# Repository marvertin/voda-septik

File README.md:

# voda-septik

Repozitář obsahuje ESP-IDF firmware a KiCad návrh hardware. Provozní dokumentace je v [firmware/README.md](firmware/README.md).

## Struktura

- `firmware/main/` – aplikace; `main/archive/` obsahuje historický referenční kód.
- `firmware/components/` – vlastní komponenty.
- `firmware/managed_components/` – externí knihovny, jejichž obsah je uložený v Gitu.
- `firmware/dependencies.lock` – přesné verze externích závislostí.
- `firmware/sdkconfig` – úplná konfigurace sestavení pro ESP32.
- `firmware/sdkconfig.defaults` – doplňující výchozí nastavení.
- `firmware/partitions.csv` – rozdělení 4MB flash paměti.
- `firmware/tools/zalevaci` – nástroj pro MQTT příkazy, diagnostiku a OTA.
- `firmware/ha/` – [podklady pro vytvoření a obnovu provozu HA a MQTT](firmware/ha/README.md), dvě samostatné Compose služby a verzovaná konfigurace bez provozních hesel.
- `hardware/` – KiCad projekt, schéma, PCB a vlastní knihovny; mapa v [hardware/README.md](hardware/README.md).
- `AGENTS.md` a `.agents/` – pracovní instrukce a mapy projektu.

## Verze a větve

- Firmware: **ESP-IDF v5.5.2**, target **esp32**. Stejnou verzi používá automatické sestavení v `.github/workflows/build.yml`.
- Hardware byl upravován v **KiCadu 9**.
- Nová funkcionalita vzniká na dočasné větvi `develop` vytvořené z `main`, nasazuje se přes USB/OTA a testuje. Po potvrzení OTA se `main` posune na skutečně provozovaný commit. Provozní opravy vznikají na `main` a ihned se nasazují; následně se přenesou do develop, pokud existuje. Po začlenění a ověření se develop smaže. Čistá dokumentace patří na main a případně existující develop bez zvýšení release verze. Úplný postup a mechanismus Git verzí jsou v [pravidlech vývoje a nasazení](firmware/docs/vyvoj-a-nasazeni.md).

Obnovu začni z `main`, pokud nepotřebuješ konkrétní vývojovou verzi. IDF ani verze knihoven se při obnově automaticky neaktualizují na novější řadu.

## Obnova na čistém počítači

### 1. Získání projektu

Nainstaluj Git a zajisti přístup ke GitHub repozitáři. Na macOS/Linuxu:

```sh
mkdir -p ~/Projects
cd ~/Projects
git clone git@github.com:marvertin/voda-septik.git
cd voda-septik
git switch main
```

Pokud nemáš nastavený SSH klíč, použij HTTPS adresu `https://github.com/marvertin/voda-septik.git` a přihlas se ke GitHubu. SSH klíče nejsou součástí tohoto repozitáře.

### 2. Instalace ESP-IDF

Použij [oficiální instalační postup pro ESP-IDF v5.5.2](https://docs.espressif.com/projects/esp-idf/en/v5.5.2/esp32/get-started/index.html) včetně systémových předpokladů pro svůj operační systém.

Pro ruční instalaci na macOS/Linuxu do umístění očekávaného projektovým `.envrc`:

```sh
mkdir -p ~/.espressif/v5.5.2
git clone --branch v5.5.2 --recursive https://github.com/espressif/esp-idf.git ~/.espressif/v5.5.2/esp-idf
cd ~/.espressif/v5.5.2/esp-idf
./install.sh esp32
```

Na Windows vyber ve vhodném instalátoru nebo rozšíření ESP-IDF verzi **v5.5.2** a otevři jeho připravený terminál. Projektové `.envrc` je určené pro macOS/Linux, není podmínkou sestavení.

Instalace IDF, překladače a Python prostředí jsou obnovitelné nástroje a do projektového Gitu nepatří.

### 3. Sestavení

Na macOS/Linuxu aktivuj IDF pro aktuální terminál:

```sh
source ~/.espressif/v5.5.2/esp-idf/export.sh
cd ~/Projects/voda-septik/firmware
idf.py --version
idf.py build
```

Ověř, že první příkaz vypíše verzi **5.5.2**. Target `esp32` je již uložený v `sdkconfig`; při obnově není potřeba spouštět `idf.py set-target`, který resetuje konfiguraci.

Výstup je `firmware/build/voda-septik.bin`. Složka `build/` se vytváří znovu a nezálohuje se v Gitu. Po přesunu projektu odstraň staré `build/`, aby nezůstaly absolutní cesty z původního umístění.

Volitelně lze použít `direnv`: nainstaluj ho, zapoj do svého shellu a v `firmware/` spusť `direnv allow`. Projektový `.envrc` přidá i `firmware/tools` do `PATH`. Při jiném umístění IDF uprav jeho cestu nebo aktivuj IDF ručně.

### 4. Nahrání přes USB

Připoj ESP32 a zjisti jeho sériový port. Z `firmware/` spusť:

```sh
idf.py -p PORT flash monitor
```

Nahraď `PORT` skutečným portem, například `/dev/cu.usbserial-…` na macOS nebo `COM3` na Windows. Monitor se ukončuje pomocí `Ctrl+]`.

Pro nahrání používej projektovou tabulku oddílů a sestavený bootloader. Příkaz `erase-flash` smaže také nastavení a provozní hodnoty uložené v zařízení; pro běžnou obnovu počítače není potřeba.

## MQTT a OTA

Nástroj `tools/zalevaci` vyžaduje Python 3; pro MQTT operace také příkazy `mosquitto_pub` a pro OTA `mosquitto_sub`. Spouštěj jej ze složky `firmware/`:

```sh
./tools/zalevaci --help
./tools/zalevaci ota --help
```

Broker a přihlašování lze nastavit parametry nástroje nebo proměnnými prostředí, například `MQTT_HOST`, `MQTT_PORT`, `MQTT_USER` a `MQTT_PASS_FILE`. Výchozí adresy brokerů jsou lokální pro původní síť a na jiném místě je potřeba je změnit.

MQTT heslo si nástroj ukládá do `~/.voda-septik/mqtt_password`. Tento soubor **není v repozitáři**: heslo uchovej ve správci hesel nebo bezpečné záloze. Nástroj si při prvním použití vyžádá chybějící heslo. Heslo nezapisuj do README ani jej nepřidávej do Gitu.

OTA používá MQTT příkazy a HTTP(S) stažení obrazu. Nový firmware po ověření funkčnosti vyžaduje potvrzení kvůli rollbacku. Aktuální rozhraní helperu popisuje `./tools/zalevaci ota --help`; interaktivní i neinteraktivní postup a rollback popisuje [firmware/docs/ota.md](firmware/docs/ota.md).

## Obnova hardware v KiCadu

1. Nainstaluj KiCad 9 a jeho standardní knihovny.
2. Otevři `hardware/Voda septik.kicad_pro`.
3. Projektové tabulky `sym-lib-table` a `fp-lib-table` připojují knihovnu `martin` přes `${KIPRJMOD}`. Díky tomu nezávisí na absolutní cestě k projektu.
4. Přes správce zásuvných modulů a obsahu nainstaluj **Espressif KiCad Libraries**. Návrh používá knihovnu s názvem `PCM_Espressif`; ověř její registraci v tabulce symbolů i footprintů. Pokud chybí, připoj odpovídající nainstalovanou knihovnu pod tímto názvem.

Použité symboly a footprinty jsou vložené také ve schématu a PCB, takže existující návrh lze otevřít. Pro aktualizace z knihoven a vkládání dalších součástek je potřeba správně připojit externí knihovny. Verze balíčku Espressif zatím není v projektu připnutá.

Automatické zálohy KiCadu, zámky a osobní nastavení editoru se v Gitu neuchovávají.

## Co zálohovat mimo Git

Git uchovává zdroje a konfiguraci pro sestavení, nikoli celý provozní stav:

- MQTT heslo a případné další přístupové údaje uložené mimo repozitář.
- Nastavení, kalibrace a čítače v ESP32: NVS a datové oddíly zařízení nejsou součástí zdrojového kódu. Pro úplnou obnovu zařízení udržuj samostatný záznam nastavení nebo zálohu jeho datových oddílů.
- Při provozování Home Assistantu také jeho úplnou zálohu. Git obsahuje YAML konfiguraci, ale ne `.storage`, databázi, uživatele a nastavení vytvořená přes UI. Obdobně případná provozní data Mosquitto vyžadují vlastní zálohu.

Konfigurace Docker Compose používá pohyblivé značky obrazů `stable` a `2`; sama nezaručuje obnovu totožné verze služeb.

Lokální commity, necommitované soubory a stashe nejsou automaticky na GitHubu. Po dokončení změn je commitni a odešli do příslušné větve. Stav ověř pomocí `git status`, `git fetch origin` a `git branch -vv`.

## Ověření obnovitelnosti

Dne **12. 10. 2026** byl nový klon větve `main` z GitHubu sestaven bez původní složky `build/` a bez necommitovaných souborů projektu. Sestavení s ESP-IDF **5.5.2** pro **ESP32** prošlo. Test použil již nainstalované nástroje; nová instalace vývojového prostředí ani flashování fyzického zařízení nebyly součástí testu.

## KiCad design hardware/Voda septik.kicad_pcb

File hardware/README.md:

# Hardware voda-septik

Stav dokumentace ověřen 12. 10. 2026. Návrh je v KiCadu 9 a související runtime firmware je v `../firmware/`.

## Soubory a knihovny

- `Voda septik.kicad_pro` – projekt; `Voda septik.kicad_sch` – schéma; `Voda septik.kicad_pcb` – deska.
- `martin.kicad_sym` a `martin.pretty/` jsou připojené jako projektová knihovna `martin` pomocí `${KIPRJMOD}`.
- `0martin.kicad_sym` a `zaciname.pretty/` jsou také v Gitu, ale současné projektové tabulky je nepřipojují jako samostatné knihovny.
- Standardní KiCad knihovny používané návrhem zahrnují `Device`, `Connector`, `Analog_ADC`, `Display_Character`, `power`, `Capacitor_THT`, `Connector_PinHeader_2.54mm`, `Diode_THT`, `LED_THT`, `Resistor_THT`.
- Externí **Espressif KiCad Libraries** nainstaluj přes správce zásuvných modulů a obsahu a ověř registraci názvu `PCM_Espressif` v tabulce symbolů i footprintů. Balíček není v repozitáři ani připnutý na konkrétní verzi.
- Schéma/PCB obsahují vložené kopie použitých symbolů/footprintů. To umožňuje otevřít stávající návrh, ale pro aktualizace a nové součástky je potřeba dostupná zdrojová knihovna.
- `.kicad_prl`, zámky a automatické zálohy jsou ignorované; `.bak`, stará schématická záloha, CSV a `fp-info-cache` jsou historicky verzované pomocné soubory.

## GPIO podle aktivního firmware

Zdrojem této tabulky je [pins.h](../firmware/main/pins.h); jde o konfiguraci programu, nikoli nezávislé elektrické ověření zapojení desky.

| Konstanta | GPIO | Poznámka v kódu |
| --- | --- | --- |
| `STATUS_LED_GPIO` | 16 | D9 LED |
| `TM1637_CLK_GPIO` | 17 | J4 CLK |
| `TM1637_DIO_GPIO` | 18 | J4 DIO |
| `DISPLAY_I2C_SDA_GPIO` | 22 | J3 SDA |
| `DISPLAY_I2C_SCL_GPIO` | 23 | J3 SCL |
| `ADS1115_I2C_SDA_GPIO` | 14 | U3 SDA |
| `ADS1115_I2C_SCL_GPIO` | 13 | U3 SCL |
| `ADS1115_ALERT_RDY_GPIO` | 4 | U3 ALERT/RDY |
| `FLOW_SENSOR_GPIO` | 33 | /prutok |
| `TEMPERATURE_SENSOR_GPIO` | 32 | /teplomery |
| `RS485_RX_GPIO` | 27 | MAX3485 TXD |
| `RS485_TX_GPIO` | 26 | MAX3485 RXD |
| `RS485_EN_GPIO` | 25 | MAX3485 EN |
| `BOOT_BUTTON_GPIO` | 0 | GPIO0 |

## Sběrnice a ADC

- ADS1115: I2C0, adresa **0x48**, 100 kHz, SDA14/SCL13, ALERT/RDY4. Jediný ADC task přepíná single-ended kanály: AIN1 tlak za filtrem, AIN2 tlak před filtrem, AIN3 hladina; AIN0 je rezerva.
- LCD HD44780 / PCF8574: samostatné I2C1, adresa **0x27**, SDA22/SCL23. Nezaměňuj ji s ADC sběrnicí.
- Proudové smyčky: firmware předpokládá **100Ω shunt**, PGA ADS1115 **±2,048 V**, LSB 62,5 µV; 4 mA → 0,4 V → RAW6400, 20 mA → 2,0 V → RAW32000. Kalibrace se ukládá v zařízení.
- RS485 / KWS-303L: UART2, **9600 8N1**, RX27/TX26, řízení směru 25, výchozí slave adresa 1.
- DS18B20: sdílená 1-Wire na GPIO32; voda a vzduch se rozlišují podle ROM adres.
- Průtok: náběžná hrana na GPIO33, výchozí 38 impulsů/l; nejde o analogový vstup.
- TM1637: CLK17/DIO18; BOOT je GPIO0, status LED GPIO16.

## Flash paměť

ESP32 má v projektu konfiguraci 4 MB. Zdrojem je [partitions.csv](../firmware/partitions.csv):

| Oddíl | Offset | Velikost | Účel |
| --- | --- | --- | --- |
| `nvs` | 0x9000 | 0x6000 | konfigurace `app_cfg`, restart metadata `sys_meta`, základ čítače `flash_ctr` |
| `otadata` | 0xF000 | 0x2000 | volba OTA obrazu |
| `phy_init` | 0x11000 | 0x1000 | PHY data |
| `flow_data0` | 0x12000 | 0x2000 | bitový flash čítač celých litrů |
| `user_data1` | 0x14000 | 0x2000 | rezervovaný datový oddíl |
| `user_data2` | 0x16000 | 0x2000 | rezervovaný datový oddíl |
| `user_data3` | 0x18000 | 0x2000 | rezervovaný datový oddíl |
| `ota_0` | 0x20000 | 0x180000 | první obraz aplikace |
| `ota_1` | 0x1A0000 | 0x180000 | druhý obraz aplikace |

Při obnově čítače nestačí samotný `flow_data0`: potřebuje i základ/rollover marker z NVS `flash_ctr`. Při přemapování oddílů, změně ADC rozsahu, adres nebo GPIO aktualizuj firmware i tuto mapu. Dokumentační průchod neprováděl měření skutečné desky.

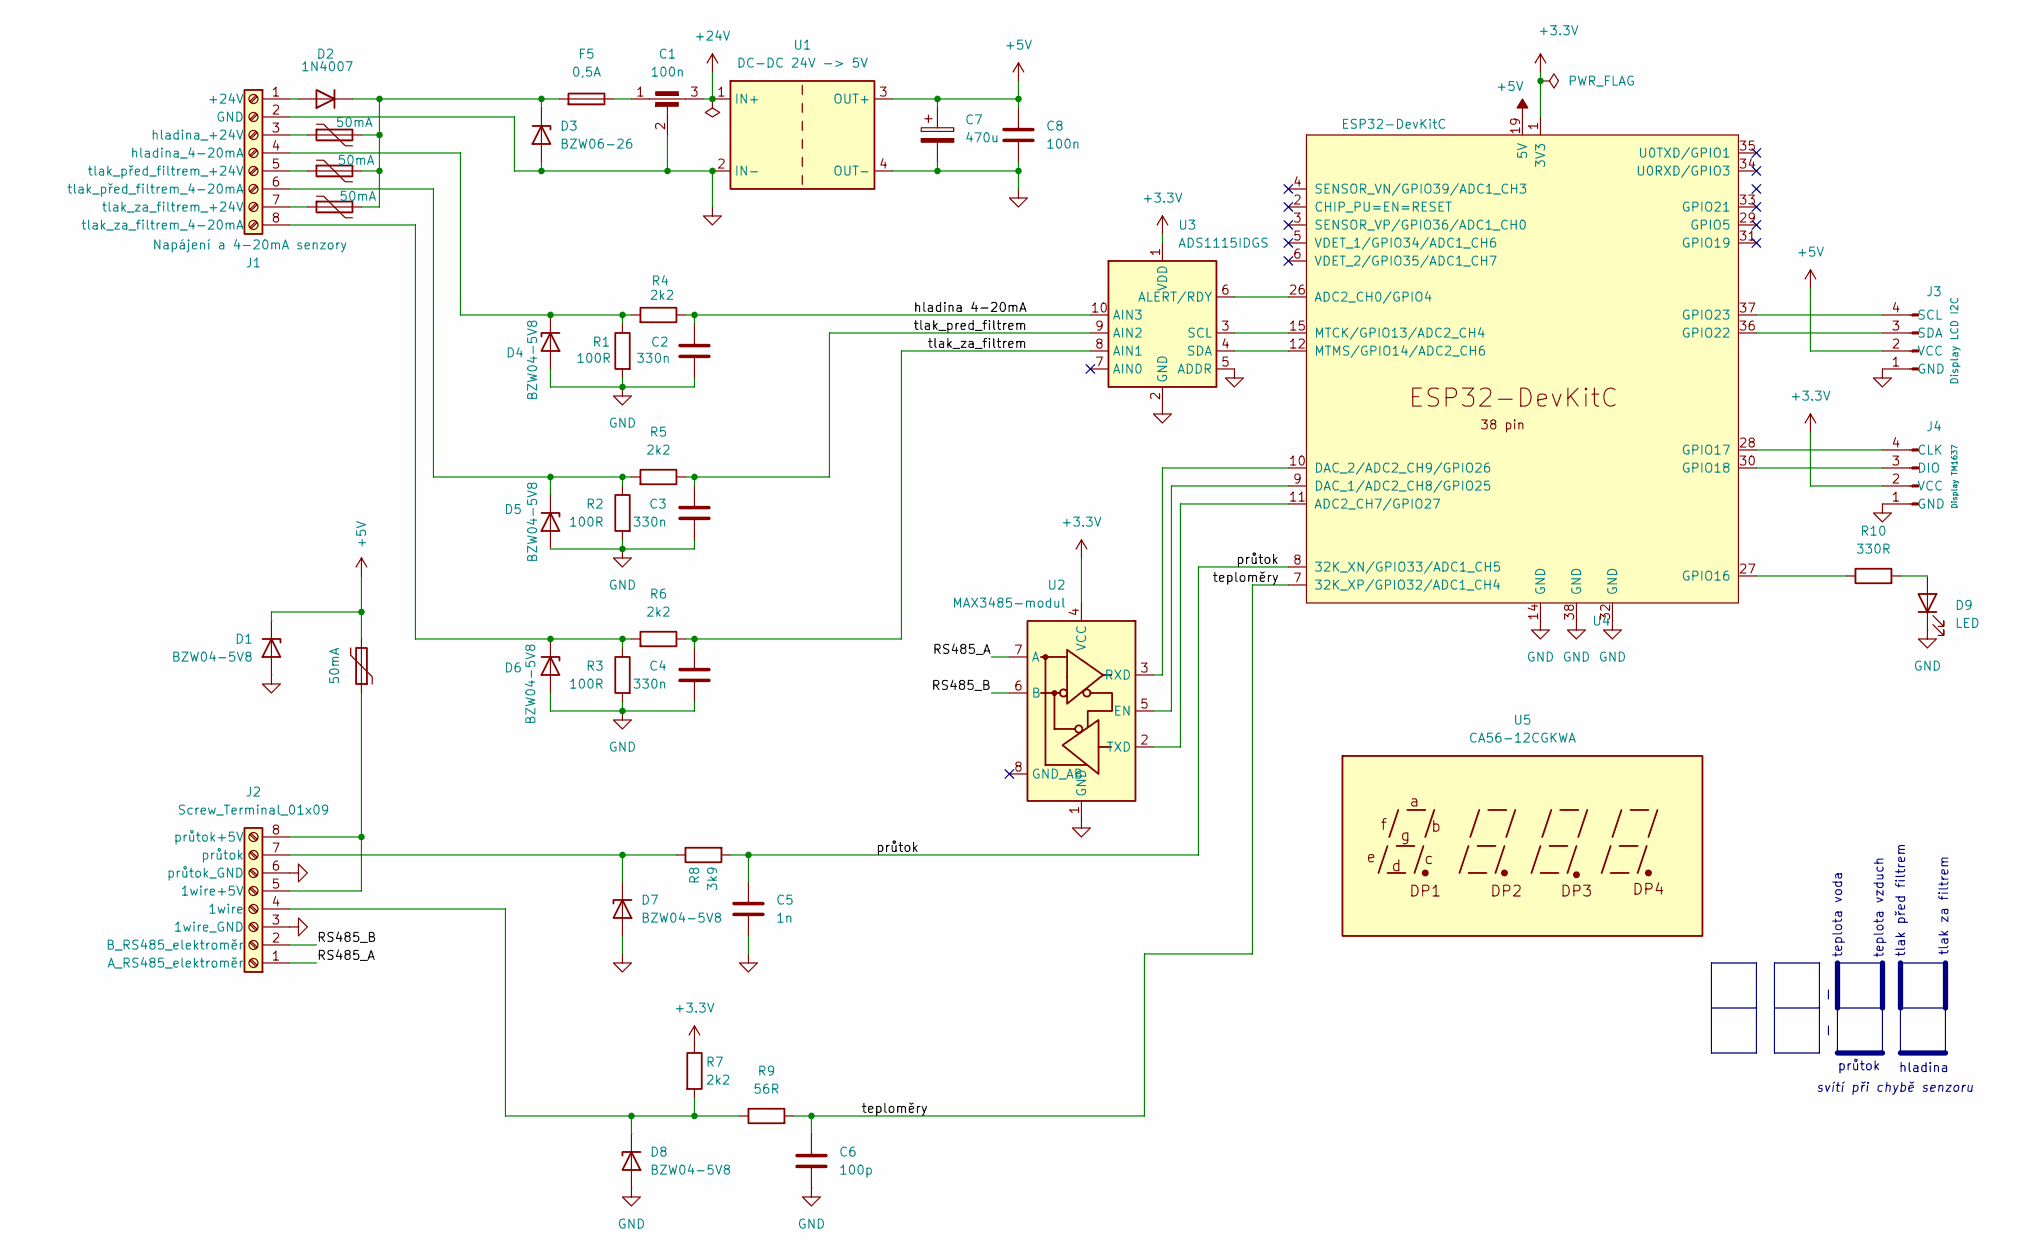
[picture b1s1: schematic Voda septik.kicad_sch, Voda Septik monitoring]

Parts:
C1: 100n; Odruseni_3x_2.54mm
C2, C3, C4: 330n; C_Disc_D5.0mm_W2.5mm_P5.00mm
C5: 1n; C_Disc_D5.0mm_W2.5mm_P5.00mm
C6: 100p; C_Disc_D5.0mm_W2.5mm_P5.00mm
C7: 470u; CP_Radial_D10.0mm_P5.00mm
C8: 100n; C_Disc_D5.0mm_W2.5mm_P5.00mm
D1, D4, D5, D6, D7, D8: BZW04-5V8; D_DO-15_P2.54mm_Vertical_AnodeUp
D2: 1N4007; D_DO-15_P2.54mm_Vertical_AnodeUp
D3: BZW06-26; D_DO-15_P2.54mm_Vertical_AnodeUp
D9: LED; LED_D3.0mm
F1, F2, F3, F4: 50mA; Fuse_Disc_D8.3_W3.8_P5.1
F5: 0,5A; Fuse_Axial_L11mm_D3.9mm_P15.24mm_Horizontal
J1: Napájení a 4-20mA senzory; Svorky_EB147A_8_5.08
J2: Screw_Terminal_01x09; Svorky_EB147A_8_5.08
J3: Display LCD I2C; PinHeader_1x04_P2.54mm_Vertical
J4: Display TM1637; PinHeader_1x04_P2.54mm_Vertical
R1, R2, R3: 100R; R_Axial_DIN0207_L6.3mm_D2.5mm_P2.54mm_Vertical
R4, R5, R6, R7: 2k2; R_Axial_DIN0207_L6.3mm_D2.5mm_P2.54mm_Vertical
R8: 3k9; R_Axial_DIN0207_L6.3mm_D2.5mm_P2.54mm_Vertical
R9: 56R; R_Axial_DIN0207_L6.3mm_D2.5mm_P2.54mm_Vertical
R10: 330R; R_Axial_DIN0207_L6.3mm_D2.5mm_P2.54mm_Vertical
U1: DC-DC 24V -> 5V; LM2596 DC-DC HW-411
U2: MAX3485-modul
U3: ADS1115IDGS; ADS1115_modul_vertical
U4: ESP32-DevKitC
U5: CA56-12CGKWA; DISPLAY_clok_MOUNT_4xM3

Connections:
+3.3V: J4.2 (VCC), R7.1, U2.4 (VCC), U3.1 (VDD), U4.1 (3V3)
+5V: C7.1, C8.1, D1.1 (K), F4.2, J3.2 (VCC), U1.3 (OUT+), U4.19 (5V)
+24V: C1.3, U1.1 (IN+)
/RS485_A: J2.1 (A_RS485_elektroměr), U2.7 (A)
/RS485_B: J2.2 (B_RS485_elektroměr), U2.6 (B)
/hladina 4-20mA: C2.1, R4.1, U3.10 (AIN3)
/průtok: C5.1, R8.2, U4.8 (32K_XN/GPIO33/ADC1_CH5)
/teploměry: C6.1, R9.2, U4.7 (32K_XP/GPIO32/ADC1_CH4)
/tlak_pred_filtrem: C3.1, R5.1, U3.9 (AIN2)
/tlak_za_filtrem: C4.1, R6.1, U3.8 (AIN1)
GND: C1.2, C2.2, C3.2, C4.2, C5.2, C6.2, C7.2, C8.2, D1.2 (A), D3.2 (A), D4.2 (A), D5.2 (A), D6.2 (A), D7.2 (A), D8.2 (A), D9.1 (K), J1.2 (GND), J2.3 (1wire_GND), J2.6 (průtok_GND), J3.1 (GND), J4.1 (GND), R1.2, R2.2, R3.2, U1.2 (IN-), U1.4 (OUT-), U2.1 (GND), U3.2 (GND), U3.5 (ADDR), U4.14 (GND), U4.32 (GND), U4.38 (GND)
unnamed: C1.1, F5.2
unnamed: D2.2 (A), J1.1 (+24V)
unnamed: D2.1 (K), D3.1 (K), F1.2, F2.2, F3.2, F5.1
unnamed: D4.1 (K), J1.4 (hladina_4-20mA), R1.1, R4.2
unnamed: D5.1 (K), J1.6 (tlak_před_filtrem_4-20mA), R2.1, R5.2
unnamed: D6.1 (K), J1.8 (tlak_za_filtrem_4-20mA), R3.1, R6.2
unnamed: D7.1 (K), J2.7 (průtok), R8.1
unnamed: D8.1 (K), J2.4 (1wire), R7.2, R9.1
unnamed: D9.2 (A), R10.2
unnamed: F1.1, J1.3 (hladina_+24V)
unnamed: F2.1, J1.5 (tlak_před_filtrem_+24V)
unnamed: F3.1, J1.7 (tlak_za_filtrem_+24V)
unnamed: F4.1, J2.5 (1wire+5V), J2.8 (průtok+5V)
unnamed: J3.4 (SCL), U4.37 (GPIO23)
unnamed: J3.3 (SDA), U4.36 (GPIO22)
unnamed: J4.4 (CLK), U4.28 (GPIO17)
unnamed: J4.3 (DIO), U4.30 (GPIO18)
unnamed: U2.5 (EN), U4.9 (DAC_1/ADC2_CH8/GPIO25)
unnamed: U2.3 (RXD), U4.10 (DAC_2/ADC2_CH9/GPIO26)
unnamed: U2.2 (TXD), U4.11 (ADC2_CH7/GPIO27)
unnamed: U3.6 (ALERT/RDY), U4.26 (ADC2_CH0/GPIO4)
unnamed: U3.3 (SCL), U4.15 (MTCK/GPIO13/ADC2_CH4)
unnamed: U3.4 (SDA), U4.12 (MTMS/GPIO14/ADC2_CH6)
unnamed: R10.1, U4.27 (GPIO16)

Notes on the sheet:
teplota vzduch
průtok
tlak před filtrem
svítí při chybě senzoru
tlak za filtrem
teplota voda
hladina

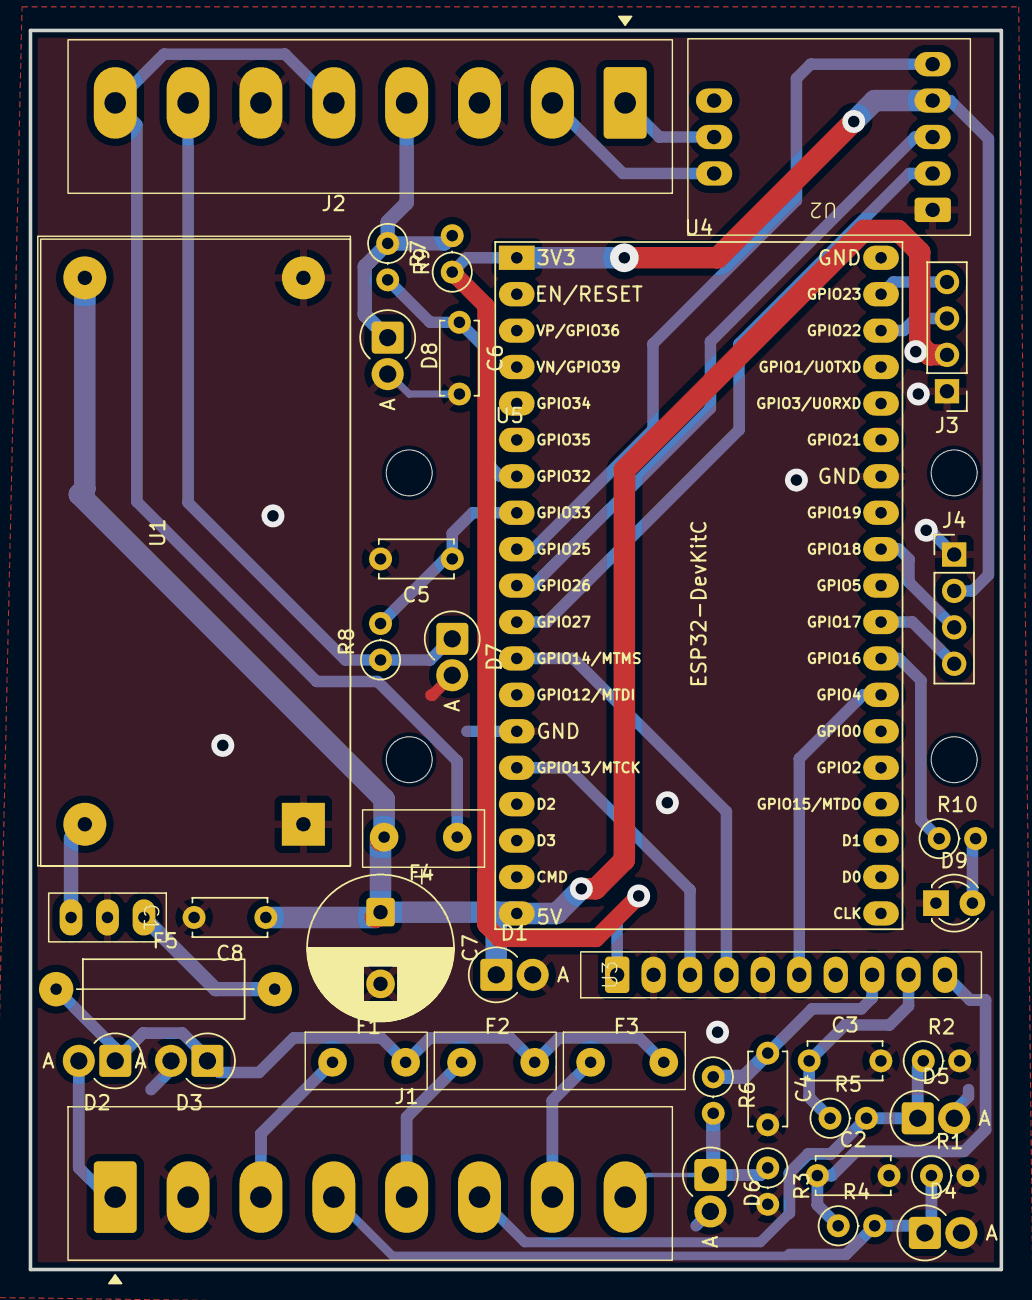
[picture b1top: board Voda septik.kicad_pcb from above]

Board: 2 copper layers, 67.7 x 86.4 mm, 41 parts (0 on the bottom side), 35 nets.

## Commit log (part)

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2026-02-11 Měření výšky hladiny.
2026-02-11 Instalace ESP_IDF přes eim install
2026-02-12 Zapisujeme na displej všechny veličiny.
2026-02-12 Funguje nějak oříznutý plovoucí průměr.
2026-02-12 Převedení do C++
2026-02-12 Převedení ořezaného průmeru na třídu.
2026-02-12 Vyřešení špatné inicializace.
2026-02-12 Inicializace wifi
2026-02-12 Heslo bere z flash.
2026-02-13 Rozchození publikace přes mqtt do HA.
2026-02-14 Konfigurační aplikace.
2026-02-14 Změna načítání configu.
2026-02-14 Počítání restartů a úvodní stránka.
2026-02-15 Příznak servisního režimu.
2026-02-15 Výpis ota partišnů.
2026-02-15 Předělán průtokoměr.
2026-02-15 Průtokoměr nějak funguje.
2026-02-15 ODstranění _demo z průtokoměru.
2026-02-22 Přidat eventy na stavy sítě.
2026-02-22 MQTT se opět nějak publikuje.
2026-02-22 Méžná o něco lepší synchronizace.
2026-02-22 Inicializace sítě architektonicky upravena, včetně MQTT.
2026-02-22 Refaktorována síť do komponenty.
2026-02-22 Už to lépe posílá offline a online statusy.
2026-02-22 Odstranit nekonečný reconnect.
2026-02-22 Vyčištení přijímání network eventů.
2026-02-22 Publikovat online mimo network_core.
2026-02-22 Úprava topiků.
2026-02-22 Při stisku boot tlačítka se otevře access point.
2026-02-22 Captive DNS funguje.
2026-02-22 Jména logovacích tagů malými písmeny.
2026-02-22 Zjednodušit začátek, žádný AP mód.
2026-02-22 Boot tlačítko v samostatném souboru.
2026-02-22 Posílání události do state managera.
2026-02-22 Blokovat rekonet v access pointu.
2026-02-22 Počítání pokusů o reconnect a úspěšných reconnectů.
2026-02-22 Vyčlenění access pointovin do jiného souboru.
2026-02-22 Ošetření chyb konzistentně.
2026-02-22 Velký refactoring, ale máme problém se čtením z nvs.
2026-02-22 Operaveno startování webové apliakce.
2026-02-22 Už se správně inicializuje mqtt
2026-02-22 Posílání RSSI
2026-02-23 10 sekund zuřivého blikání po chybě.
2026-02-23 Zavedení makra APP_ERROR_CHECK
2026-02-23 První nástřel zobrazení chybového kódu na displeji.
2026-02-23 Inicializace displeje na začátku.
2026-02-23 Vyvedení ovládání displeje do samostatného souboru.
2026-02-23 Další blikání kvůli wifi.
2026-02-23 Zobrazování na sedmisegmentovém displeji stav.
2026-02-24 Startovací sekvence verze 1
2026-02-24 Startovací animace je v komponentě.
2026-02-24 Návrh struktury topiků
2026-02-24 Publikace teploty vody převedena na nový systém.
2026-02-24 Publikace online a offline je také ponovu.
2026-02-24 Další čidla přidána.
2026-02-24 Mem set promazat strukturu.
2026-02-24 Při změně stavu reflush.
2026-02-24 Předělat událost network:_core, aby změna síťování se vždy projevila.
2026-02-24 Znovu všechno přeposlat.
2026-02-24 Nějak to funguje, ale displej bliká.
2026-02-24 AP mód indikován na displeji.
2026-02-24 Commandy přes MQTT
2026-02-24 Skript pro ovládání přes mqtt.
2026-02-25 Znovu zařazení obsluhy čidel.
2026-02-25 Zdá se, že OTA základním způsobem funguje.
2026-02-25 Logy
2026-02-25 Už fungujíccí OTA.
2026-02-25 Ota posílá eventy jak to běží.
2026-02-25 Monitoruje průběh ota přes mqtt
2026-02-25 Nastavování logovacích úrovní pomocí mqtt a skriptu.
2026-02-25 Dokumentace OTA a logování.
2026-02-25 ODstranění nadbytečných logů v commandech.
2026-02-25 Odstranění servisního režimu
2026-02-25 Rebot po OTA.
2026-02-25 Oprava E102
2026-02-25 Led nesmí blikat, když máme mqtt.
2026-02-25 Udělání prázdné funkce pro blikání a zapojení, implementace je jen logování.
2026-02-25 Ledka hezky poblikává.
2026-02-25 Dočest kód pro poblikávání displeje.
2026-02-25 KDyž je polámaný senzor, posílat prázdno a ne nesmysl.
2026-02-25 U nepřipojeného teplotního čidla se také posílá null.
2026-02-25 Na displej se zobrazuje stav čidel.
2026-02-26 Vyřešení problémů se zpomaléným stavovým managerem a plnou frontou.
2026-02-26 Dobugování přes makro a zjednodušit.
2026-02-26 Úklid topiků a defaultně je web apliakce vypnutá.
2026-02-26 Obíhající segmenty při flow.
2026-02-26 Zeslabování jasu nějak funguje.
2026-02-26 Opravit snižování jasu displeje.
2026-02-26 Čtení dvou teplot funguje, ale zatím náhodně.
2026-02-26 Vyčištění varování
2026-02-26 Přejmenování na voda septik.
2026-02-26 Sloučení obslužného nástroje do jednoho.
2026-02-26 sdconfig do gitu
2026-02-26 SDkconfig změněný de gitu.
2026-02-26 Přejmenování projektu
2026-02-26 Do gitu nástroje
2026-02-26 Dokončení přejmenování
2026-02-26 Doplnění zalevaci o subscribe
2026-02-27 Úklid v pinech
2026-02-27 Odstranění LCD demo
2026-02-27 Pevně dané adresy vody a vzduchu.
2026-02-27 Teplota už není demo
2026-02-27 Odstranění demo názvů.
2026-02-27 Něco se děje s tlakem.
2026-02-28 Popřejmenování na objem.
2026-02-28 Velké přejmenování
2026-02-28 Zdá se, že to po refaktoringu funguje.
2026-02-28 Tlak
2026-02-28 Tlak na 0DB
2026-02-28 Inicializace ošetřena chyby
2026-02-28 Přejmenování logovacích tagů.
2026-02-28 Rozumné logoací úrobvně.
2026-02-28 Změnit commandy
2026-02-28 Publikování diagnostik
2026-03-01 Přidat watchdog
2026-03-01 Mít k dispozici i raw hodnotu.
2026-03-01 Úprava výšky hladiny.
2026-03-01 Předělání konfigurace a defaultních hodnot.
2026-03-01 Sekce v konfiguraci.
2026-03-01 Vypisovat defaulty a klíče ve webové aplikaci.
2026-03-01 Ještě pročištění zaásoby.
2026-03-01 Debug na tři místa.
2026-03-01 Krajní hodnoty
2026-03-01 ADC čtení je teď lepší.
2026-03-01 Vypnout pořád dělané discovery.
2026-03-01 Hlášení senzorů je v pořádku kromě tlaků.
2026-03-01 Tlak už funguje.
2026-03-01 Pryč špatný debug.
2026-03-01 Discovery do HA
2026-03-01 Hoe asistent je tady
2026-03-01 Při poruše senzoru musí být neavailabilní
2026-03-01 Přejmenování availability topiků.
2026-03-02 přesun pod firmware
2026-03-06 Schéma, ale jen té krabičky.
2026-03-07 LED je na jiném PIN
2026-03-07 Přečíslování
2026-03-07 Jakési jiné spouštění AP.
2026-03-07 Podmíněné vyřazení LCD
2026-03-07 Piny pro teploty
2026-03-07 ADC přesměrovat.
2026-03-07 Opravy chyb segmentů i jiné.
2026-03-07 V průtokoměru si hlídat průtok.
2026-03-07 Provést enqueue u discovery topiků.
2026-03-07 Watch dogy, publikace, displej neinicializvoat.
2026-03-08 Odlaďování, piny.
2026-03-08 Průtokoměr
2026-03-08 Histereze opravena v hladině.
2026-03-08 Upravena hystereze
2026-03-08 Doladění průtoku a schematu.
2026-03-08 Upravit schéma podle skutečnosti.
2026-03-08 Omezit logování kde je zbytečné.
2026-03-08 Simulace průtokoměru.
2026-03-08 Průtokoměr také zmizí při vypnutí.
2026-03-08 Zádné simulace.
2026-03-19 Úprava schématu, asi popisky.
2026-04-01 Před kalibrace hodnot
2026-04-02 Čtení z elektroměru
2026-04-03 Už funguje čtení z barevného elektroměru.
2026-04-03 Už to čte ze dvou měřáků, ale je v tom bordel.
2026-04-03 Refaktorováno na o něco hezčí kód.
2026-04-03 Máme tam čas
2026-04-03 Už vypadá dobře hlavní cyklus.
2026-04-04 I účiník i energie máme.
2026-04-04 Dobře měříme i reaktivní hodnoty.
2026-04-04 Přejmenování zdrojáků s elektroměry.
2026-04-04 Ťení energie, ale dvěma dotazy.
2026-04-04 Čtení energie jedním dotazem.
2026-04-04 Přejmenování proměnných
2026-04-04 Už je připraveno čtení z měřáků.
2026-04-05 Kalibrace průtokoměru.
2026-04-05 APliakci webovou sputit i po resetu, pokud je vyvolán formwarem.
2026-04-07 Add GitHub Actions workflow for ESP-IDF firmware build
    Agent-Logs-Url: https://github.com/marvertin/voda-septik/sessions/8a3eb7e9-b0a2-4647-8775-75f9fab76fb8
2026-04-07 Metření přes externí ADC funguje.
2026-04-07 Knihovna pro ads111
2026-04-07 Použít knihovnu ads111x
2026-04-08 Simulace průtokoměru pomocí pinu
2026-04-08 Přeházení pinů.
2026-04-08 Úprava schématu
2026-04-11 Vyvéjíme PCB a jsme v v koncích díky malé krabičce.
2026-04-14 Tak už to mám všechno naroutováno
2026-04-15 Hotový návrh desky a schématu, které jdou do výroby.
2026-04-15 Dokončení schématu a návrhu PCB o stavu, který byl poslán do výroby.
2026-04-15 DS_Store se nedává do gitu.
2026-04-15 Github actions prubina
2026-04-15 Změna názvu pkonstanty pinů úrp display, prootže přijdou i jiné I2C
2026-04-15 Refactoring výpočtu pulsů, aby to bylo přehlednější.
2026-04-15 Průtok počítat adaptivně.
2026-04-15 Simulovaný průtokoměr funguje.
2026-04-15 Flexibilní simulátor.
2026-04-15 Zkrátíme dobu ustavení průtokoměru na 1 a půl sekundy.
2026-04-15 Čtení z ADS1115 se musí v hlavním programu zařadit.
2026-04-15 Knihovna ADS111x a závislost na ní, zatím není použita.
2026-04-15 Přehození LCD na I2C_NUM_1. Netuším proč jsme to udělali, asi AI.
2026-04-15 Zkoušení čtení z ADS1115, z pinů na kterých to je se to nikdy nepoužilo.
2026-04-21 Udělat hezčí schéma aby se tak nekřížily vývody
2026-04-21 Přemapování pinů podle nového schématu na desce.
2026-04-22 Opravit umístění textů na PCB, aby se to nepletlo.
2026-04-22 Opravit čtení a ads1115
2026-04-22 Elektromer funguje.
2026-04-22 Dostáváme ready z čtení ADS1115 a funguje to.
2026-04-22 Dokreslit propojku RDY/ALERT
2026-04-24 Implement ADS1115 sampling task
2026-05-01 Komentáře, konstanty místo čísel.
2026-05-01 Napojení na nový ADS pro tlak.
2026-05-01 Elektroměr funguje.
2026-05-01 Přečíslování chybových kódů.
2026-05-01 Doplnění jakési diagnostiky.
2026-05-01 Opravit počet startů.
2026-05-01 Čítače MQTT a jiné.
2026-05-01 Pop restartu web aplikaci spustit jken když byla před tím.
2026-05-01 Odsteranění ůlzných dem.
